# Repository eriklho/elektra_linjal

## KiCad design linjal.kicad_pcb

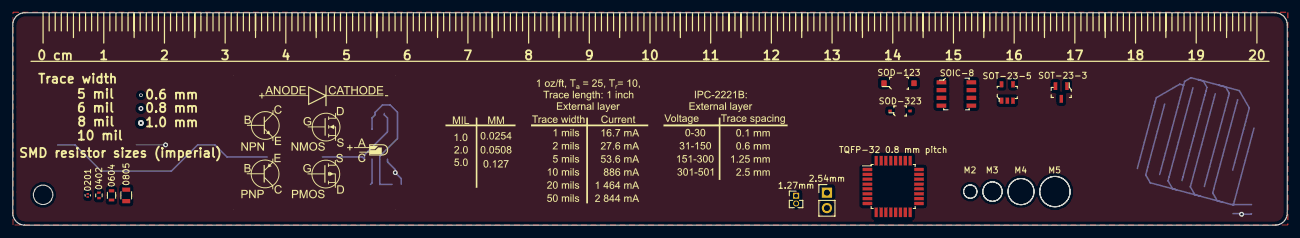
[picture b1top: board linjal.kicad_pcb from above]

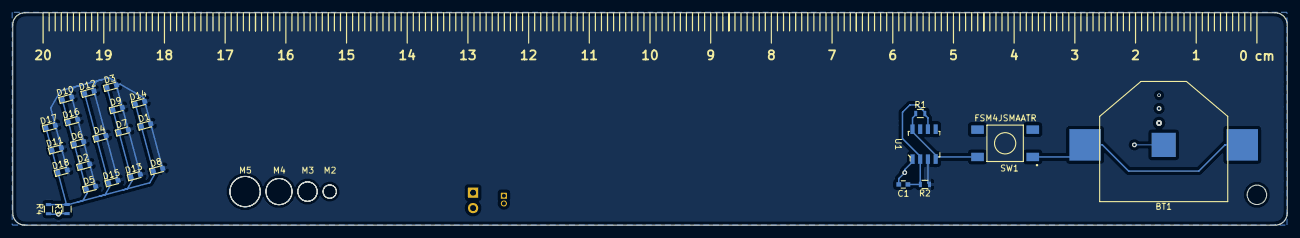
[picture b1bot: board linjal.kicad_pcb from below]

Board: 2 copper layers, 210.0 x 35.0 mm, 47 parts (31 on the bottom side), 6 nets.

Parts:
1.27mm: Pin_Header_Straight_1x02_Pitch1.27mm
2.54mm: Pin_Header_Straight_1x02_Pitch2.54mm
0201: R_0201
0402: R_0402
0604: R_0603
0805: R_0805
BT1: BC-2001
C1: 300n; C_0603
D1, D2, D3, D4, D5, D6, D7, D8, D9, D10, D11, D12, D13, D14, D15, D16, D17, D18: LED; LED_0603
M2, M2#2: MountingHole_2.2mm_M2
M3, M3#2, M3#3: MountingHole_3.2mm_M3
M4, M4#2: MountingHole_4.3mm_M4
M5, M5#2: MountingHole_5mm
R1: 1M; R_0603
R2: 20k; R_0603
R3, R4: 10R; R_0603
SOD-123: SOD-123
SOD-323: SOD-323
SOIC-8: 8-SOIC
SOT-23-3: SOT-23-3
SOT-23-5: SOT-23-5
SW1: FSM4JSMAATR; SW_FSM4JSMAATR
TQFP-32 0.8 mm pitch: TQFP-32_7x7mm_Pitch0.8mm
U1: LM555; 8-SOIC

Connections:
GND: BT1.2, C1.2, R3.1, R4.1, U1.1
unnamed: BT1.1, SW1.1
unnamed: C1.1, R1.2, R2.2, U1.2, U1.6
unnamed: D1.1, D2.1, D3.1, D4.1, D5.1, D6.1, D7.1, D8.1, D9.1, D10.1, D11.1, D12.1, D13.1, D14.1, D15.1, D16.1, D17.1, D18.1, R3.2, R4.2
unnamed: D1.2, D2.2, D3.2, D4.2, D5.2, D6.2, D7.2, D8.2, D9.2, D10.2, D11.2, D12.2, D13.2, D14.2, D15.2, D16.2, D17.2, D18.2, R2.1, U1.3
unnamed: R1.1, SW1.2, U1.4, U1.8

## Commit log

2018-08-09 Init repo
2018-08-09 finished schematic. rough drawing of layout
2018-08-10 added some footprints
